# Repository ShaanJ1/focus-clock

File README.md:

# Focus Clock
A small battery powered pomorodo clock that can help you manage your time better. Includes pomorodo timer, custom timer support, screen time reminders, and more!

### Showcase
*Coming soon...*
### Bill of Materials (BOM)

| **Item Name**                                                       | **URL**                                                                                                               | **Price** | **Quantity** |
|-------------------------------------------------------------------- |-----------------------------------------------------------------------------------------------------------------------|-----------|--------------|
| SSD1306 OLED Display                                                | [AliExpress](https://www.aliexpress.com/item/1005008640132638.html)                                                   | $5.58     | 1            |
| Rotary Encoder                                                      | [AliExpress](https://www.aliexpress.com/item/1005009532009840.html)                                                   | $14.23    | 1            |
| Vibration Motor                                                     | [DigiKey](https://www.digikey.ca/en/products/detail/adafruit-industries-llc/1201/5353637)                             | $2.82     | 1            |
| Speaker Driver                                                      | [DigiKey](https://www.digikey.ca/en/products/detail/dfrobot/DFR0299/6588463)                                          | $8.53     | 1            | 
| Speaker                                                             | [DigiKey](https://www.digikey.ca/en/products/detail/soberton-inc/SP-1605-5/8600809)                                   | $3.36     | 1            |
| 3.7V Battery (self provided, not included in total)                 | -                                                                                                                     | $0.00     | 1            |
| Adafruit Battery Charger (self provided, not included in total)     | -                                                                                                                     | $0.00     | 1            |
| 1x2 Male Pin Connector                                              | [DigiKey](https://www.digikey.ca/en/products/detail/w-rth-elektronik/61300211121/4846823)                             | $1.48     | 10           |
| 1x3 Male Pin Connector                                              | [DigiKey](https://www.digikey.ca/en/products/detail/adam-tech/PH1-03-UA/9830289)                                      | $0.15     | 1            |
| 1x4 Male Pin Connector                                              | [DigiKey](https://www.digikey.ca/en/products/detail/adam-tech/PH1-04-UA/9829296)                                      | $0.15     | 1            |
| 1x5 Male Pin Connector                                              | [DigiKey](https://www.digikey.ca/en/products/detail/adam-tech/PH1-05-UA/9830343)                                      | $0.15     | 1            |
| 2x3 Male Pin Connector                                              | [DigiKey](https://www.digikey.ca/en/products/detail/adam-tech/PH2-06-UA/9830396)                                      | $0.18     | 1            |
| PushButton                                                          | [DigiKey](https://www.digikey.ca/en/products/detail/same-sky-formerly-cui-devices-/TS02-66-43-BK-100-LCR-D/15634359)  | $0.45     | 3            |
| PCBA                                                                | [JLCPCB](https://jlcpcb.com/)                                                                                         | $35.78    | 1            |

**Total (CAD):** $72.86

**Total (USD):** $52.92

### Images
Schematic

PCB

Assembly

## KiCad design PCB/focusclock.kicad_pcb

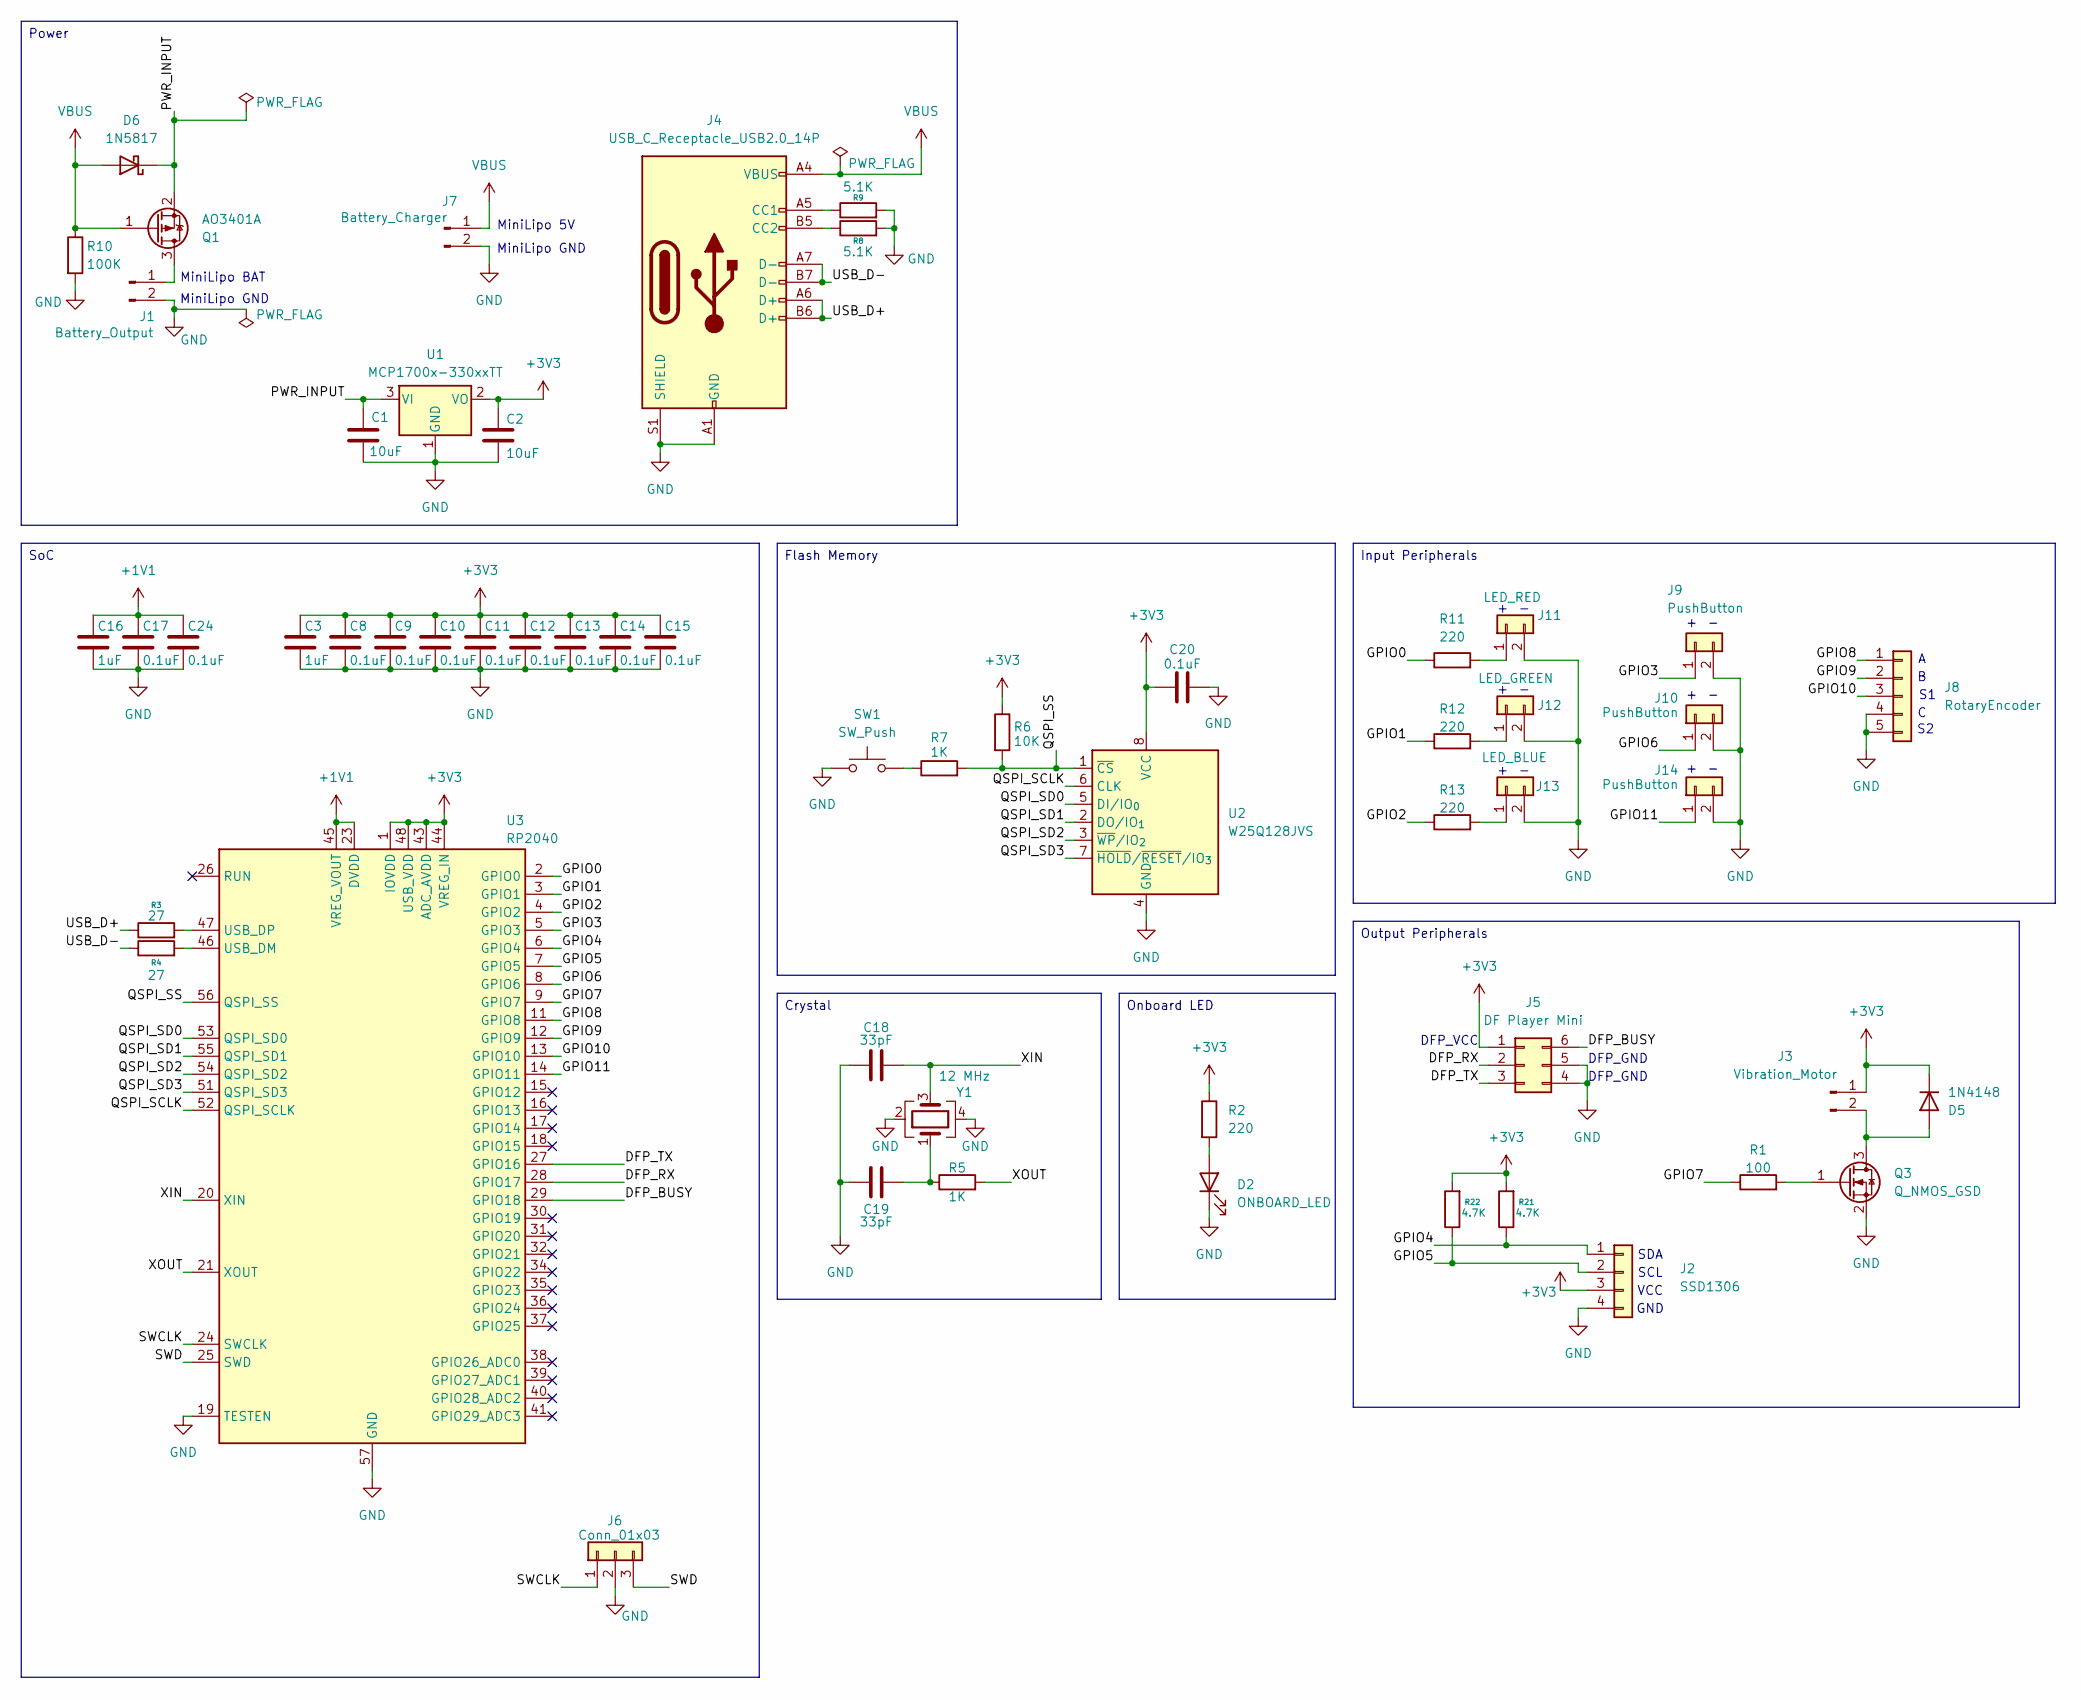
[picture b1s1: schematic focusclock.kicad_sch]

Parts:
C1, C2: 10uF; C_0603_1608Metric
C3, C16: 1uF; C_0402_1005Metric
C8, C9, C10, C11, C12, C13, C14, C15, C17, C20, C24: 0.1uF; C_0402_1005Metric
C18, C19: 33pF; C_0402_1005Metric
D2: ONBOARD_LED; LED_0402_1005Metric
D5: 1N4148; D_DO-35_SOD27_P7.62mm_Horizontal
D6: 1N5817; D_DO-41_SOD81_P10.16mm_Horizontal
J1: Battery_Output; PinHeader_1x02_P2.54mm_Vertical
J2: SSD1306; PinHeader_1x04_P2.54mm_Vertical
J3: Vibration_Motor; PinHeader_1x02_P2.54mm_Vertical
J4: USB_C_Receptacle_USB2.0_14P; USB_C_Receptacle_HRO_TYPE-C-31-M-12
J5: DF Player Mini; PinHeader_2x03_P2.54mm_Vertical
J6: Conn_01x03; PinHeader_1x03_P2.54mm_Vertical
J7: Battery_Charger; PinHeader_1x02_P2.54mm_Vertical
J8: RotaryEncoder; PinHeader_1x05_P2.54mm_Vertical
J9, J10, J14: PushButton; PinHeader_1x02_P2.54mm_Vertical
J11: LED_RED; PinHeader_1x02_P2.54mm_Vertical
J12: LED_GREEN; PinHeader_1x02_P2.54mm_Vertical
J13: LED_BLUE; PinHeader_1x02_P2.54mm_Vertical
Q1: AO3401A; SOT-23
Q3: Q_NMOS_GSD; SOT-23
R1: 100; R_0402_1005Metric
R2, R11, R12, R13: 220; R_0402_1005Metric
R3, R4: 27; R_0402_1005Metric
R5, R7: 1K; R_0402_1005Metric
R6: 10K; R_0402_1005Metric
R8, R9: 5.1K; R_0402_1005Metric
R10: 100K; R_0402_1005Metric
R21, R22: 4.7K; R_0402_1005Metric
SW1: SW_Push; SW_Push_SPST_NO_Alps_SKRK
U1: MCP1700x-330xxTT; SOT-23
U2: W25Q128JVS; SOIC-8_5.3x5.3mm_P1.27mm
U3: RP2040; QFN-56-1EP_7x7mm_P0.4mm_EP3.2x3.2mm
Y1: 12 MHz; Crystal_SMD_3225-4Pin_3.2x2.5mm

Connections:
+1V1: C16.1, C17.1, C24.1, U3.23 (DVDD), U3.45 (VREG_VOUT), U3.50 (DVDD)
+3V3: C2.1, C3.1, C8.1, C9.1, C10.1, C11.1, C12.1, C13.1, C14.1, C15.1, C20.1, D5.1 (K), J2.3, J3.1, J5.1, R2.1, R6.1, R21.2, R22.2, U1.2 (VO), U2.8 (VCC), U3.1 (IOVDD), U3.10 (IOVDD), U3.22 (IOVDD), U3.33 (IOVDD), U3.42 (IOVDD), U3.43 (ADC_AVDD), U3.44 (VREG_IN), U3.48 (USB_VDD), U3.49 (IOVDD)
/DFP_BUSY: J5.6, U3.29 (GPIO18)
/DFP_RX: J5.2, U3.28 (GPIO17)
/DFP_TX: J5.3, U3.27 (GPIO16)
/GPIO0: R11.1, U3.2 (GPIO0)
/GPIO1: R12.1, U3.3 (GPIO1)
/GPIO2: R13.1, U3.4 (GPIO2)
/GPIO3: J9.1, U3.5 (GPIO3)
/GPIO4: J2.1, R21.1, U3.6 (GPIO4)
/GPIO5: J2.2, R22.1, U3.7 (GPIO5)
/GPIO6: J10.1, U3.8 (GPIO6)
/GPIO7: R1.1, U3.9 (GPIO7)
/GPIO8: J8.1, U3.11 (GPIO8)
/GPIO9: J8.2, U3.12 (GPIO9)
/GPIO10: J8.3, U3.13 (GPIO10)
/GPIO11: J14.1, U3.14 (GPIO11)
/PWR_INPUT: C1.1, D6.1 (K), Q1.2 (S), U1.3 (VI)
/QSPI_SCLK: U2.6 (CLK), U3.52 (QSPI_SCLK)
/QSPI_SD0: U2.5 (DI/IO_{0}), U3.53 (QSPI_SD0)
/QSPI_SD1: U2.2 (DO/IO_{1}), U3.55 (QSPI_SD1)
/QSPI_SD2: U2.3 (~WP/IO_{2}), U3.54 (QSPI_SD2)
/QSPI_SD3: U2.7 (~HOLD/~RESET/IO_{3}), U3.51 (QSPI_SD3)
/QSPI_SS: R6.2, R7.2, U2.1 (~CS), U3.56 (QSPI_SS)
/SWCLK: J6.1, U3.24 (SWCLK)
/SWD: J6.3, U3.25 (SWD)
/USB_D+: J4.A6 (D+), J4.B6 (D+), R3.1
/USB_D-: J4.A7 (D-), J4.B7 (D-), R4.1
/XIN: C18.2, U3.20 (XIN), Y1.3
/XOUT: R5.2, U3.21 (XOUT)
GND: C1.2, C2.2, C3.2, C8.2, C9.2, C10.2, C11.2, C12.2, C13.2, C14.2, C15.2, C16.2, C17.2, C18.1, C19.1, C20.2, C24.2, D2.1 (K), J1.2, J2.4, J4.A1 (GND), J4.A12 (GND), J4.B1 (GND), J4.B12 (GND), J4.S1 (SHIELD), J5.4, J5.5, J6.2, J7.2, J8.4, J8.5, J9.2, J10.2, J11.2, J12.2, J13.2, J14.2, Q3.2 (S), R8.2, R9.2, R10.2, SW1.1, U1.1 (GND), U2.4 (GND), U3.19 (TESTEN), U3.57 (GND), Y1.2, Y1.4
unnamed: C19.2, R5.1, Y1.1
unnamed: D2.2 (A), R2.2
unnamed: D5.2 (A), J3.2, Q3.3 (D)
unnamed: J1.1, Q1.3 (D)
unnamed: J4.A5 (CC1), R8.1
unnamed: J4.B5 (CC2), R9.1
unnamed: J11.1, R11.2
unnamed: J12.1, R12.2
unnamed: J13.1, R13.2
unnamed: Q3.1 (G), R1.2
unnamed: R7.1, SW1.2
unnamed: R4.2, U3.46 (USB_DM)
unnamed: R3.2, U3.47 (USB_DP)
VBUS: D6.2 (A), J4.A4 (VBUS), J4.A9 (VBUS), J4.B4 (VBUS), J4.B9 (VBUS), J7.1, Q1.1 (G), R10.1

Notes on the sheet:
DFP_GND
MiniLipo GND
GND
DFP_VCC
SCL
VCC
MiniLipo 5V
MiniLipo BAT
SDA
Input Peripherals
Crystal
SoC
Power
Output Peripherals
Onboard LED
Flash Memory

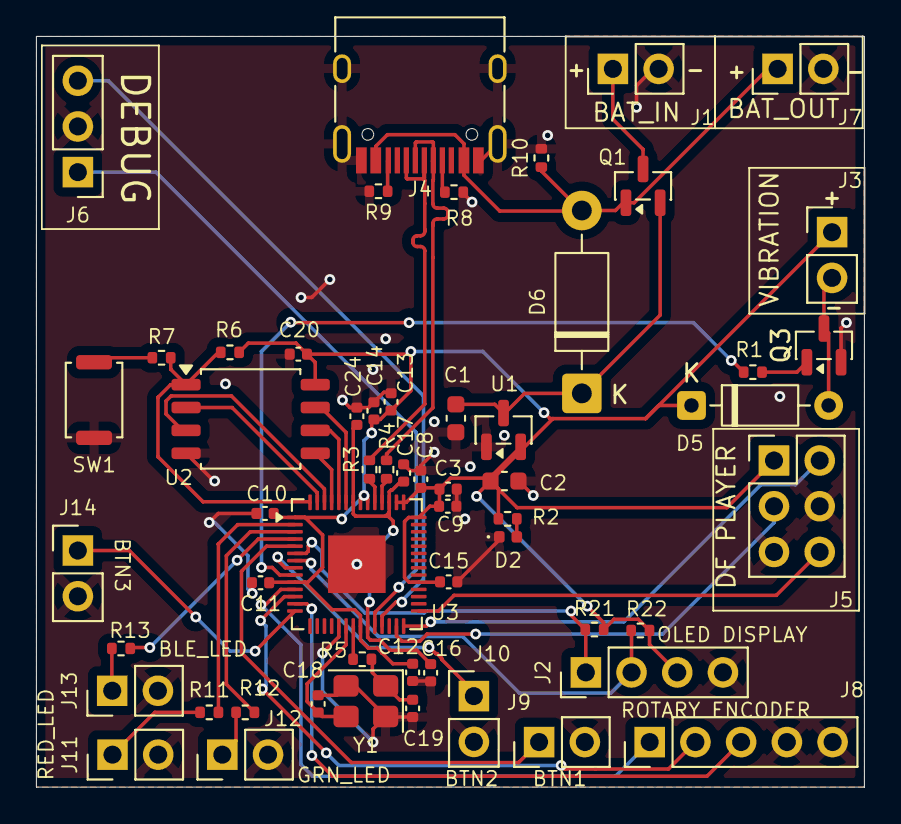
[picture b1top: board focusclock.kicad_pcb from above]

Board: 2 copper layers, 46.0 x 41.7 mm, 56 parts (0 on the bottom side), 45 nets.

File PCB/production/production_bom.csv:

Designator,Footprint,Quantity,Value,LCSC Part #
"C1, C2",0603,2,10uF,
"C10, C11, C12, C13, C14, C15, C17, C20, C24, C8, C9",0402,11,0.1uF,
"C16, C3",0402,2,1uF,
"C18, C19",0402,2,33pF,
D2,0402,1,ONBOARD_LED,
D5,D_DO-35_SOD27_P7.62mm_Horizontal,1,1N4148,
D6,D_DO-41_SOD81_P10.16mm_Horizontal,1,1N5817,
J1,PinHeader_1x02_P2.54mm_Vertical,1,Battery_Output,
"J10, J14, J9",PinHeader_1x02_P2.54mm_Vertical,3,PushButton,
J11,PinHeader_1x02_P2.54mm_Vertical,1,LED_RED,
J12,PinHeader_1x02_P2.54mm_Vertical,1,LED_GREEN,
J13,PinHeader_1x02_P2.54mm_Vertical,1,LED_BLUE,
J2,PinHeader_1x04_P2.54mm_Vertical,1,SSD1306,
J3,PinHeader_1x02_P2.54mm_Vertical,1,Vibration_Motor,
J4,USB_C_Receptacle_HRO_TYPE-C-31-M-12,1,USB_C_Receptacle_USB2.0_14P,
J5,PinHeader_2x03_P2.54mm_Vertical,1,DF Player Mini,
J6,PinHeader_1x03_P2.54mm_Vertical,1,Conn_01x03,
J7,PinHeader_1x02_P2.54mm_Vertical,1,Battery_Charger,
J8,PinHeader_1x05_P2.54mm_Vertical,1,RotaryEncoder,
Q1,SOT-23,1,AO3401A,
Q3,SOT-23,1,Q_NMOS_GSD,
R1,0402,1,100,
R10,0402,1,100K,
"R11, R12, R13, R2",0402,4,220,
"R21, R22",0402,2,4.7K,
"R3, R4",0402,2,27,
"R5, R7",0402,2,1K,
R6,0402,1,10K,
"R8, R9",0402,2,5.1K,
SW1,SW_Push_SPST_NO_Alps_SKRK,1,SW_Push,
U1,SOT-23,1,MCP1700x-330xxTT,
U2,SOIC-8_5.3x5.3mm_P1.27mm,1,W25Q128JVS,
U3,QFN-56-1EP_7x7mm_P0.4mm_EP3.2x3.2mm,1,RP2040,
Y1,Crystal_SMD_3225-4Pin_3.2x2.5mm,1,12 MHz,
